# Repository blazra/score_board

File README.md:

# Score Board

Originally designed for summer camp with a space theme. Boards were used to keep track of points kids got during the camp.

Features:
- ATtiny13A
- 2 rows of 10 LEDs in 1206 package
- 4 corner LEDs in 1206 package
- 1 center APA102-2020 RGB LED
- 3 general purpose buttons + reset
- Powered from JST XH 2 pin connector or on-board CR2032

Schematic: [hardware/score_board.pdf](hardware/score_board.pdf)

Example use-case:

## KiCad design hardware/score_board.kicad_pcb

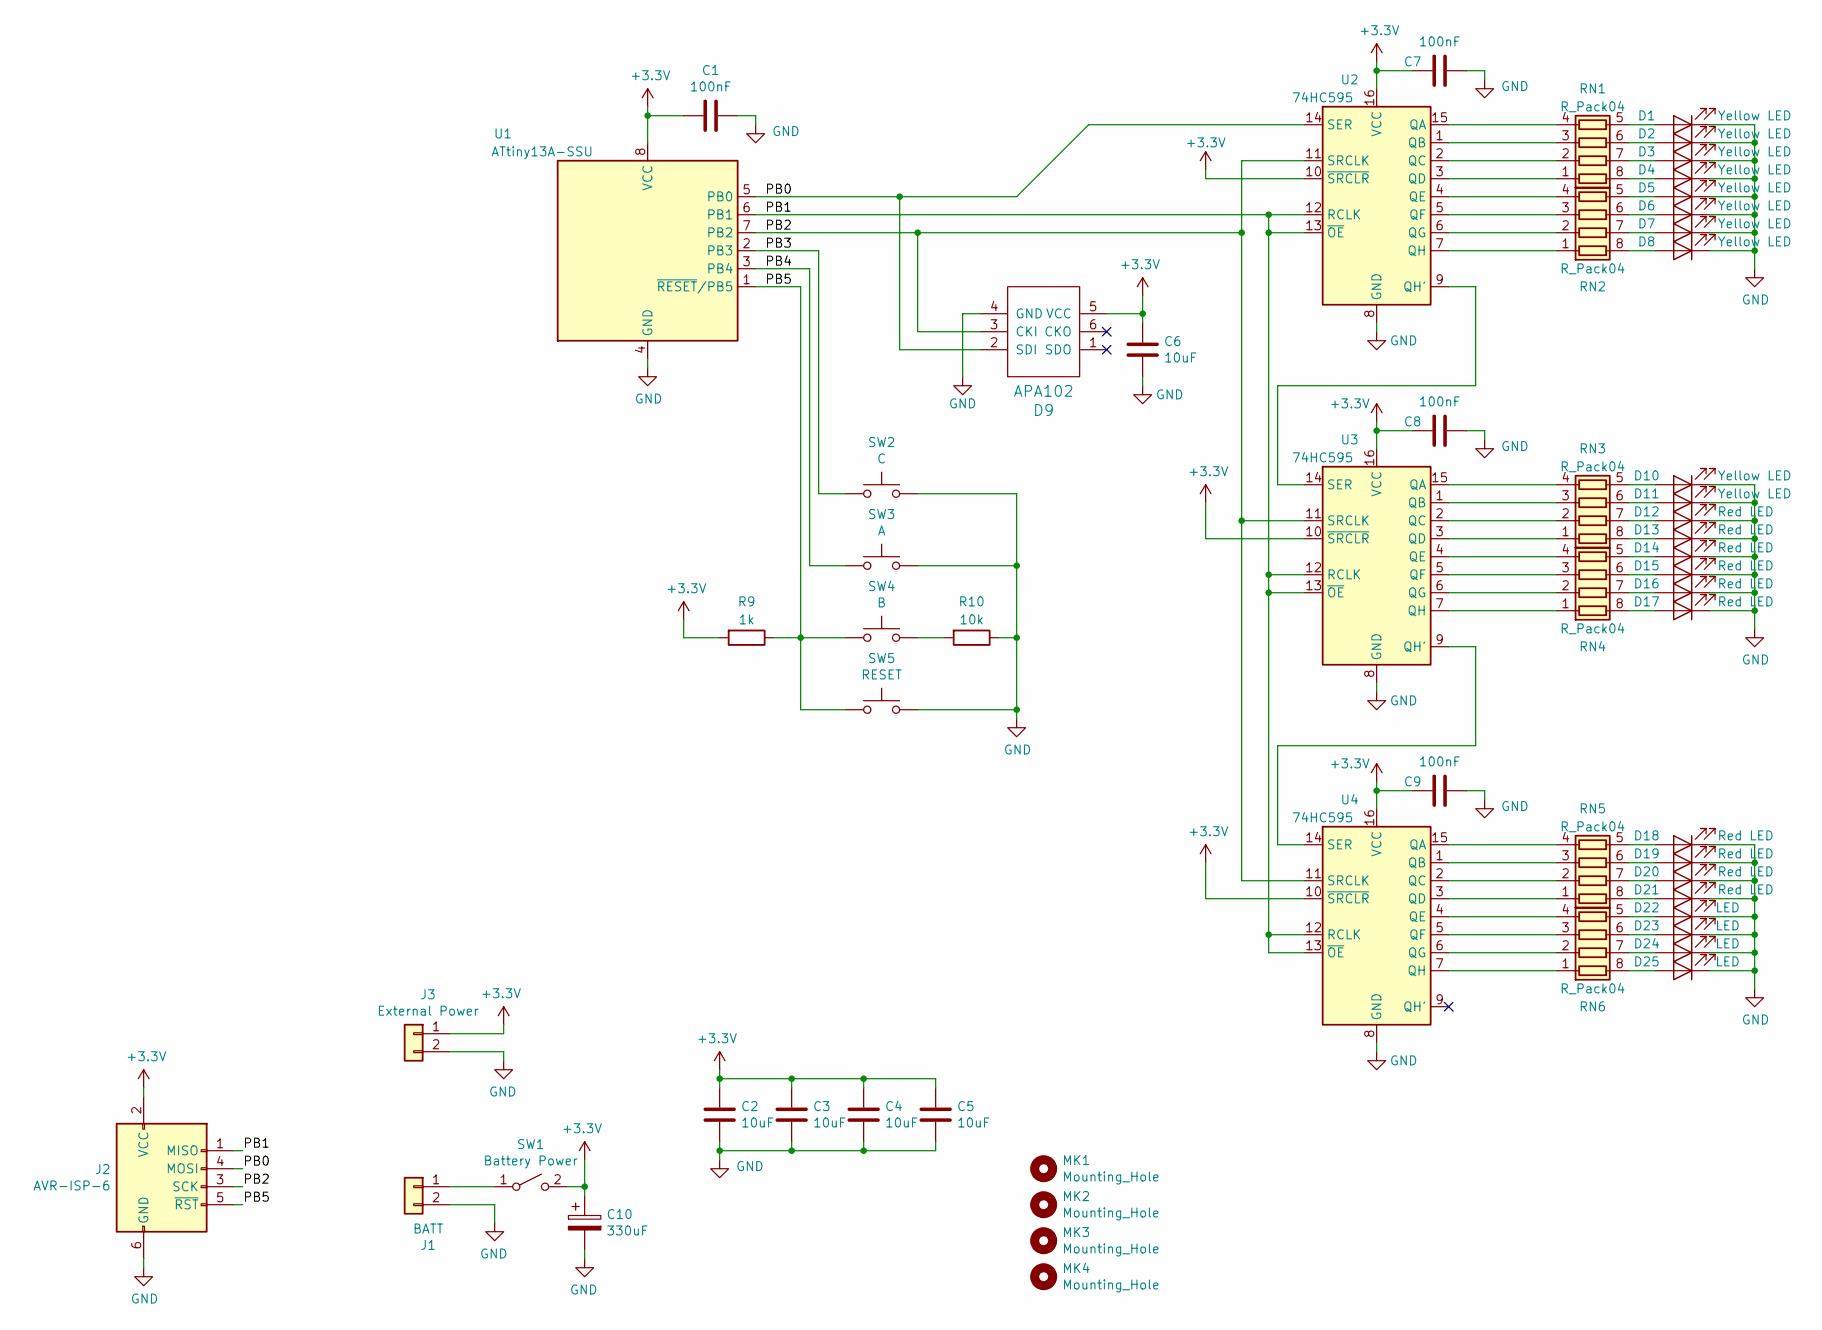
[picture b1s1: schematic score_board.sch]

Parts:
C1, C7, C8, C9: 100nF; C_0805_2012Metric
C2, C3, C4, C5, C6: 10uF; C_0805_2012Metric
C10: 330uF; CP_Elec_6.3x5.8
D1, D2, D3, D4, D5, D6, D7, D8, D10, D11: Yellow LED; LED_1206_3216Metric_Castellated
D9: APA102; APA102-2020
D12, D13, D14, D15, D16, D17, D18, D19, D20, D21: Red LED; LED_1206_3216Metric_Castellated
D22, D23, D24, D25: LED; LED_1206_3216Metric_Castellated
J1: BATT; BatteryHolder_Keystone_1058_1x2032
J2: AVR-ISP-6; PinHeader_2x03_P2.54mm_Vertical_SMD
J3: External Power; JST XH SMD 2P
MK1, MK2, MK3, MK4: Mounting_Hole; MountingHole_3.2mm_M3
R9: 1k; R_0805_2012Metric_Pad1.29x1.40mm_HandSolder
R10: 10k; R_0805_2012Metric_Pad1.29x1.40mm_HandSolder
RN1, RN2, RN3, RN4, RN5, RN6: R_Pack04; R_Array_Convex_4x0603
SW1: Battery Power; SW_SPDT_PCM12
SW2: C; SW_SPST_PTS645
SW3: A; SW_SPST_PTS645
SW4: B; SW_SPST_PTS645
SW5: RESET; SW_SPST_PTS645
U1: ATtiny13A-SSU; SOIC-8_3.9x4.9mm_P1.27mm
U2, U3, U4: 74HC595; SOIC-16_3.9x9.9mm_P1.27mm

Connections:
+3V3: C1.2, C2.2, C3.2, C4.2, C5.2, C6.2, C7.2, C8.2, C9.2, C10.1, D9.5 (VCC), J2.2 (VCC), J3.1, R9.2, SW1.2 (B), U1.8 (VCC), U2.10 (~SRCLR), U2.16 (VCC), U3.10 (~SRCLR), U3.16 (VCC), U4.10 (~SRCLR), U4.16 (VCC)
/PB0: D9.2 (SDI), J2.4 (MOSI), U1.5 (PB0), U2.14 (SER)
/PB1: J2.1 (MISO), U1.6 (PB1), U2.12 (RCLK), U2.13 (~OE), U3.12 (RCLK), U3.13 (~OE), U4.12 (RCLK), U4.13 (~OE)
/PB2: D9.3 (CKI), J2.3 (SCK), U1.7 (PB2), U2.11 (SRCLK), U3.11 (SRCLK), U4.11 (SRCLK)
/PB3: SW2.1, U1.2 (PB3)
/PB4: SW3.1, U1.3 (PB4)
/PB5: J2.5 (~RST), R9.1, SW4.1, SW5.1, U1.1 (~RESET~/PB5)
GND: C1.1, C2.1, C3.1, C4.1, C5.1, C6.1, C7.1, C8.1, C9.1, C10.2, D1.1 (K), D2.1 (K), D3.1 (K), D4.1 (K), D5.1 (K), D6.1 (K), D7.1 (K), D8.1 (K), D9.4 (GND), D10.1 (K), D11.1 (K), D12.1 (K), D13.1 (K), D14.1 (K), D15.1 (K), D16.1 (K), D17.1 (K), D18.1 (K), D19.1 (K), D20.1 (K), D21.1 (K), D22.1 (K), D23.1 (K), D24.1 (K), D25.1 (K), J1.2, J2.6 (GND), J3.2, R10.1, SW2.2, SW3.2, SW5.2, U1.4 (GND), U2.8 (GND), U3.8 (GND), U4.8 (GND)
unnamed: D1.2 (A), RN1.5 (R4.2)
unnamed: D2.2 (A), RN1.6 (R3.2)
unnamed: D3.2 (A), RN1.7 (R2.2)
unnamed: D4.2 (A), RN1.8 (R1.2)
unnamed: D5.2 (A), RN2.5 (R4.2)
unnamed: D6.2 (A), RN2.6 (R3.2)
unnamed: D7.2 (A), RN2.7 (R2.2)
unnamed: D8.2 (A), RN2.8 (R1.2)
unnamed: D10.2 (A), RN3.5 (R4.2)
unnamed: D11.2 (A), RN3.6 (R3.2)
unnamed: D12.2 (A), RN3.7 (R2.2)
unnamed: D13.2 (A), RN3.8 (R1.2)
unnamed: D14.2 (A), RN4.5 (R4.2)
unnamed: D15.2 (A), RN4.6 (R3.2)
unnamed: D16.2 (A), RN4.7 (R2.2)
unnamed: D17.2 (A), RN4.8 (R1.2)
unnamed: D18.2 (A), RN5.5 (R4.2)
unnamed: D19.2 (A), RN5.6 (R3.2)
unnamed: D20.2 (A), RN5.7 (R2.2)
unnamed: D21.2 (A), RN5.8 (R1.2)
unnamed: D22.2 (A), RN6.5 (R4.2)
unnamed: D23.2 (A), RN6.6 (R3.2)
unnamed: D24.2 (A), RN6.7 (R2.2)
unnamed: D25.2 (A), RN6.8 (R1.2)
unnamed: J1.1, SW1.1 (A)
unnamed: R10.2, SW4.2
unnamed: RN1.1 (R1.1), U2.3 (QD)
unnamed: RN1.2 (R2.1), U2.2 (QC)
unnamed: RN1.3 (R3.1), U2.1 (QB)
unnamed: RN1.4 (R4.1), U2.15 (QA)
unnamed: RN2.1 (R1.1), U2.7 (QH)
unnamed: RN2.2 (R2.1), U2.6 (QG)
unnamed: RN2.3 (R3.1), U2.5 (QF)
unnamed: RN2.4 (R4.1), U2.4 (QE)
unnamed: RN3.1 (R1.1), U3.3 (QD)
unnamed: RN3.2 (R2.1), U3.2 (QC)
unnamed: RN3.3 (R3.1), U3.1 (QB)
unnamed: RN3.4 (R4.1), U3.15 (QA)
unnamed: RN4.1 (R1.1), U3.7 (QH)
unnamed: RN4.2 (R2.1), U3.6 (QG)
unnamed: RN4.3 (R3.1), U3.5 (QF)
unnamed: RN4.4 (R4.1), U3.4 (QE)
unnamed: RN5.1 (R1.1), U4.3 (QD)
unnamed: RN5.2 (R2.1), U4.2 (QC)
unnamed: RN5.3 (R3.1), U4.1 (QB)
unnamed: RN5.4 (R4.1), U4.15 (QA)
unnamed: RN6.1 (R1.1), U4.7 (QH)
unnamed: RN6.2 (R2.1), U4.6 (QG)
unnamed: RN6.3 (R3.1), U4.5 (QF)
unnamed: RN6.4 (R4.1), U4.4 (QE)
unnamed: U2.9 (QH'), U3.14 (SER)
unnamed: U3.9 (QH'), U4.14 (SER)

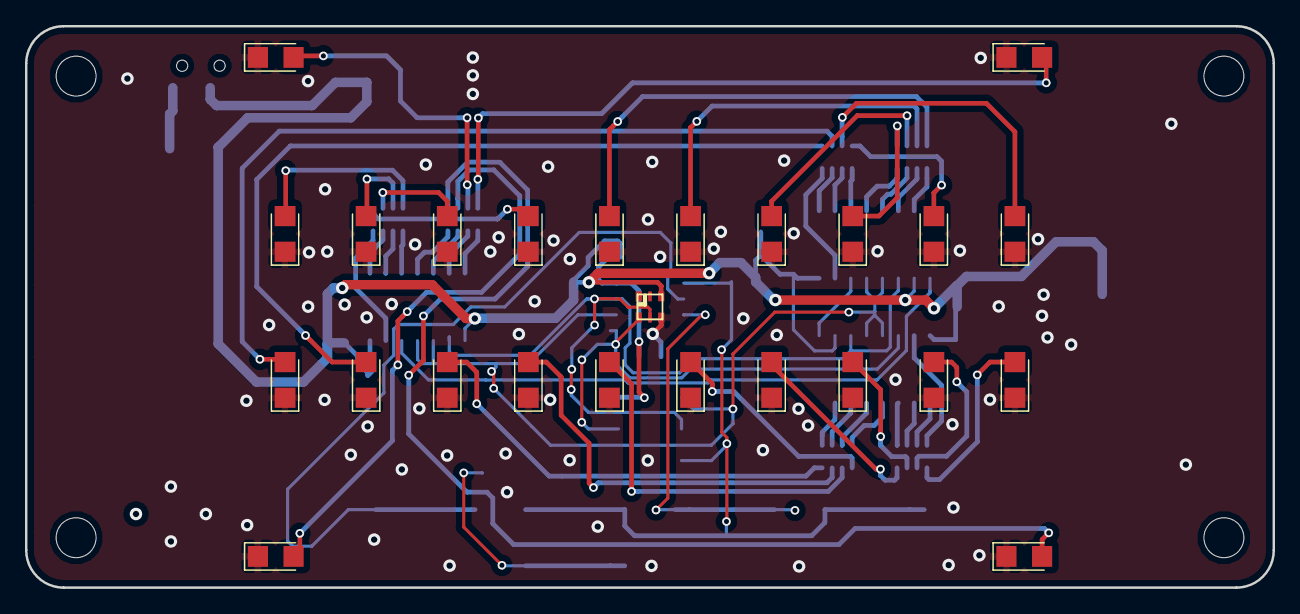
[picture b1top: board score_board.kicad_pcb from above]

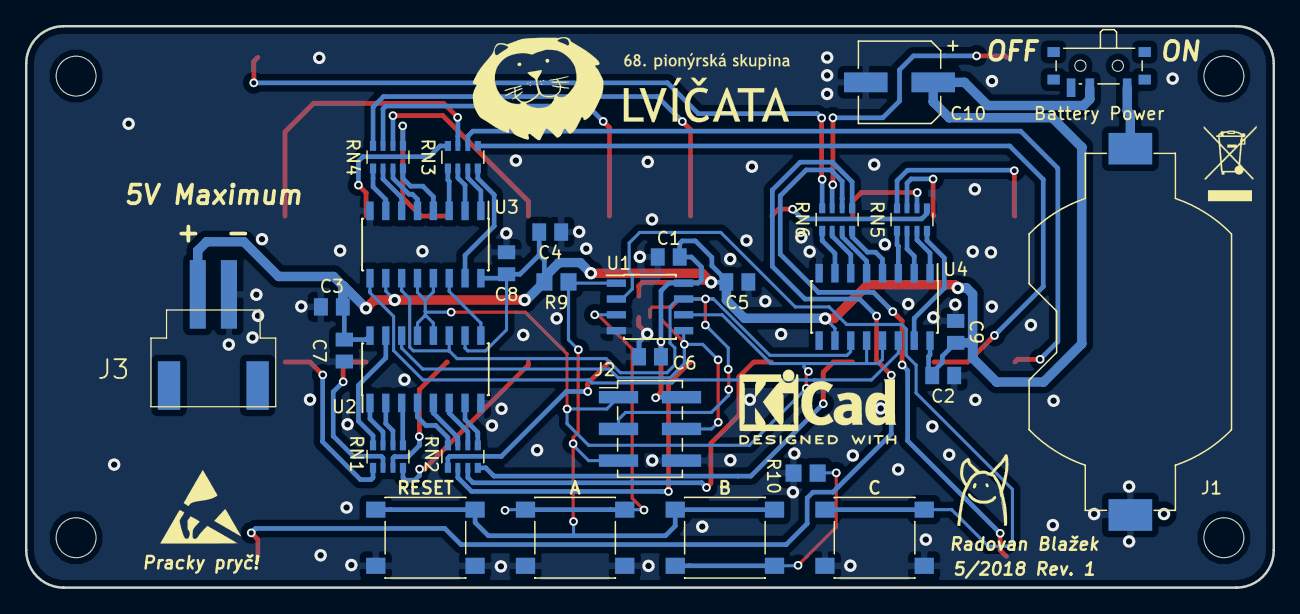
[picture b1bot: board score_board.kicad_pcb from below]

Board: 2 copper layers, 100.0 x 45.0 mm, 59 parts (30 on the bottom side), 60 nets.

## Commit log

2018-05-27 Initial commit; Score function works
2018-09-13 add RGB led compatibility
2018-09-13 change behaviour, so you can set any LED to be on or off
2019-06-16 Add .hex output file
2019-06-16 Add hardware and new dir structure
2019-06-16 Remove moved files
2019-06-16 Add images
2019-06-16 Fix some kicad libraries issues
2019-06-16 Add schematic in pdf
2019-06-16 Add photo of example use-case
